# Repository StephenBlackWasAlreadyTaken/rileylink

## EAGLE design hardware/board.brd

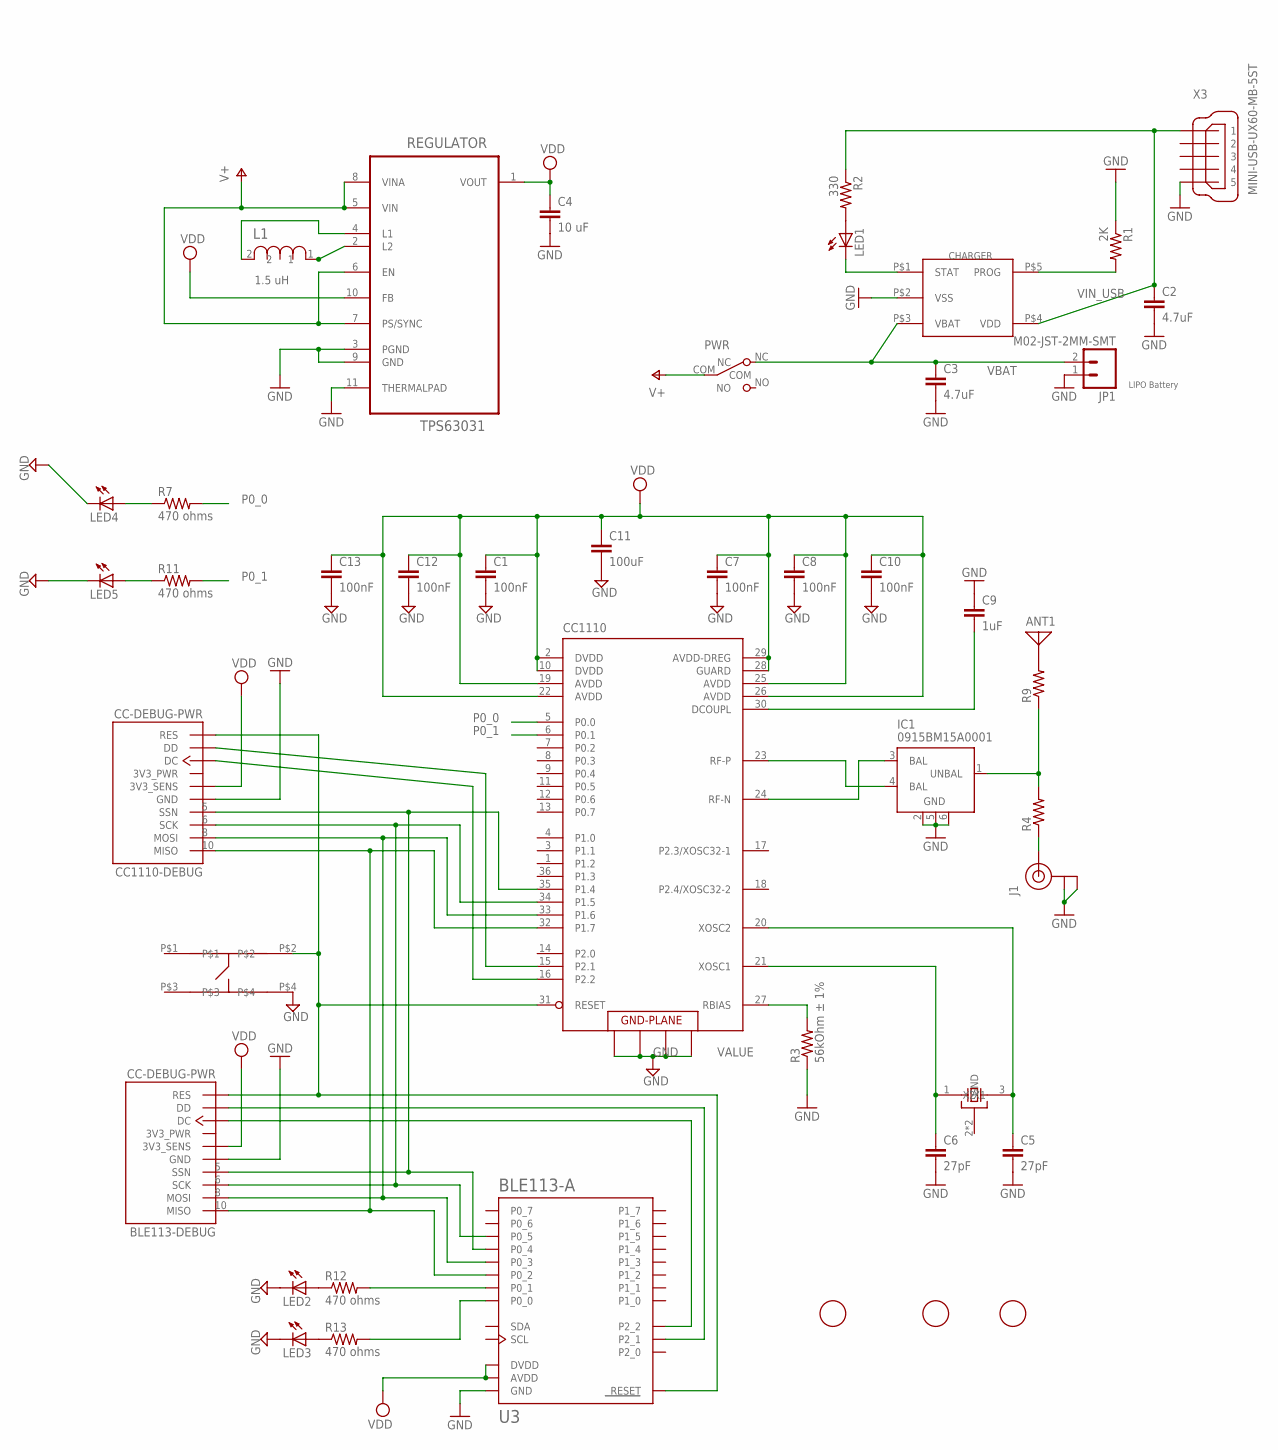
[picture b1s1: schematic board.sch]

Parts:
ANT1: ANTENNA; PAD-01
BLE113-DEBUG: CC-DEBUG-PWR; CC-P05
C1, C7, C8, C10, C12, C13: 100nF; C0402
C2: 4.7uF; C0402K
C3: 4.7uF; C0603K
C4: 10 uF; C0805K
C5, C6: 27pF; C0402K
C9: 1uF; C0402K
C11: 100uF; C0402
CC1110: CC1110; QLP-36_UPDATE
CC1110-DEBUG: CC-DEBUG-PWR; CC-P05
CHARGER: MCP73831; 5PIN_SOT23
FID1, FID2, FID3: FIDUCIAL; FIDUCIAL_1MM
IC1: 0915BM15A0001
J1: U.FL
JP1: M02-JST-2MM-SMT; JST-2-SMD
L1: 1.5 uH; INDC1610X12N
LED1, LED2, LED3, LED4, LED5: LEDSML0603; SML0603
PWR: SW_SLIDE; SLIDE_SWITCH_SMD
R1: 2K; R0402
R2: 330; R0402
R3: 56kOhm ± 1%; R0402
R4, R9: R-US_R0402; R0402
R7, R11, R12, R13: 470 ohms; R0402
REGULATOR: TPS63031; SON50P260X260X80-11N; MPN TPS63031
U3: BLE113-A
U$2: TACTILE_SWITCH; PTS540
X1: 26MHz 10pF 10ppm -20C +70C; CTS_32X25
X3: MINI-USB-UX60-MB-5ST; UX60-MB-5ST

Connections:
DC: CC1110.16 (P2.2), CC1110-DEBUG.3 (DC)
DC_BLE: BLE113-DEBUG.3 (DC), U3.P2_2
DD: CC1110.15 (P2.1), CC1110-DEBUG.4 (DD)
DD_BLE: BLE113-DEBUG.4 (DD), U3.P2_1
GND: BLE113-DEBUG.1 (GND), C1.2, C2.2, C3.2, C4.2, C5.2, C6.2, C7.2, C8.2, C9.1, C10.2, C11.2, C12.2, C13.2, CC1110.37 (GND), CC1110.38 (GND), CC1110.39 (GND), CC1110.40 (GND), CC1110-DEBUG.1 (GND), CHARGER.P$2 (VSS), IC1.2 (GND), IC1.5 (GND), IC1.6 (GND), J1.P$1 (GND), J1.P$2 (GND), JP1.1 (2), LED2.C, LED3.C, LED4.C, LED5.C, R1.1, R3.1, REGULATOR.3 (PGND), REGULATOR.9 (GND), REGULATOR.11 (THERMALPAD), U3.GND, U3.GND@2 (GND), U3.GND@3 (GND), U3.GND@4 (GND), U3.GND@5 (GND), U3.GND@6 (GND), U3.GND@7 (GND), U3.GND@8 (GND), U3.GND@9 (GND), U3.GND@10 (GND), U$2.P$4, X1.2 (GND), X1.4 (GND), X3.5
MISO: BLE113-DEBUG.10 (MISO), CC1110.32 (P1.7), CC1110-DEBUG.10 (MISO), U3.P0_2
MOSI: BLE113-DEBUG.8 (MOSI), CC1110.33 (P1.6), CC1110-DEBUG.8 (MOSI), U3.P0_3
unnamed: L1.1, REGULATOR.2 (L2)
unnamed: CHARGER.P$1 (STAT), LED1.C
unnamed: CHARGER.P$5 (PROG), R1.2
unnamed: LED1.A, R2.2
unnamed: CC1110.24 (RF-N), IC1.3 (BAL)
unnamed: L1.2, REGULATOR.4 (L1)
unnamed: CC1110.23 (RF-P), IC1.4 (BAL)
unnamed: J1.P$3 (SIGNAL), R4.1
unnamed: IC1.1 (UNBAL), R4.2, R9.1
unnamed: ANT1.1, R9.2
unnamed: CC1110.27 (RBIAS), R3.2
unnamed: C9.2, CC1110.30 (DCOUPL)
unnamed: C6.1, CC1110.21 (XOSC1), X1.1 (X1)
unnamed: C5.1, CC1110.20 (XOSC2), X1.3 (X2)
unnamed: LED4.A, R7.1
unnamed: LED5.A, R11.1
unnamed: LED2.A, R12.1
unnamed: LED3.A, R13.1
unnamed: R12.2, U3.P0_1
unnamed: R13.2, U3.P0_0
P0_0: CC1110.5 (P0.0), R7.2
P0_1: CC1110.6 (P0.1), R11.2
RESET: BLE113-DEBUG.7 (RES), CC1110.31 (RESET), CC1110-DEBUG.7 (RES), U3.RESET, U$2.P$2
SCK: BLE113-DEBUG.6 (SCK), CC1110.34 (P1.5), CC1110-DEBUG.6 (SCK), U3.P0_5
SSN: BLE113-DEBUG.5 (SSN), CC1110.35 (P1.4), CC1110-DEBUG.5 (SSN), U3.P0_4
V+: PWR.COM, REGULATOR.5 (VIN), REGULATOR.6 (EN), REGULATOR.7 (PS/SYNC), REGULATOR.8 (VINA)
VBAT: C3.1, CHARGER.P$3 (VBAT), JP1.2 (1), PWR.NC
VDD: BLE113-DEBUG.2 (3V3_SENS), C1.1, C4.1, C7.1, C8.1, C10.1, C11.1, C12.1, C13.1, CC1110.2 (DVDD), CC1110.10 (DVDD), CC1110.19 (AVDD), CC1110.22 (AVDD), CC1110.25 (AVDD), CC1110.26 (AVDD), CC1110.28 (GUARD), CC1110.29 (AVDD-DREG), CC1110-DEBUG.2 (3V3_SENS), REGULATOR.1 (VOUT), REGULATOR.10 (FB), U3.AVDD, U3.DVDD
VIN_USB: C2.1, CHARGER.P$4 (VDD), R2.1, X3.1

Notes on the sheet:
LIPO Battery

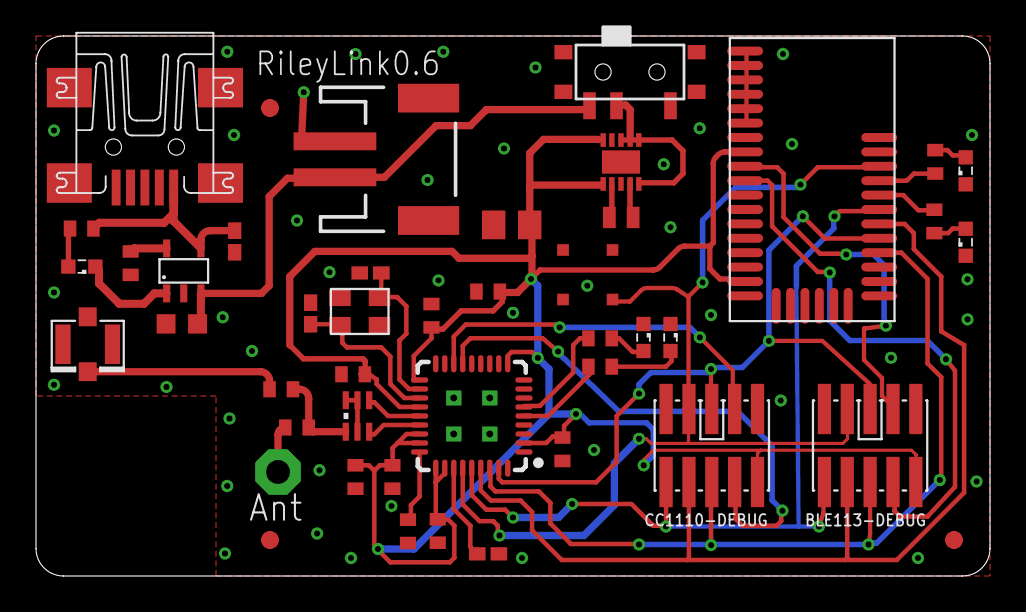
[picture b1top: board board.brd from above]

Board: 2 copper layers, 53.0 x 30.0 mm, 45 parts (0 on the bottom side), 36 nets.

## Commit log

2015-05-24 added uart file, and awful call to transmit data to test
2015-05-24 made it actually send the value instead of a placeholder
2015-05-24 transmit packets over uart once full packet is received
2015-05-29 stuck
2015-06-15 some edits made by jason

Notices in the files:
parts and their libraries:
parts: Package design from "pretty-eagle-libs" at https://github.com/esden/pretty-eagle-libs/blob/master/pel_misc.lbr by @esden at Github. (CC-BY-SA-3.0)
SparkFun-Connectors: Licensing: Creative Commons ShareAlike 4.0 International - https://creativecommons.org/licenses/by-sa/4.0
